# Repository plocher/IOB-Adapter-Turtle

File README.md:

# IOB-Adapter-Generic
## License: CERN Open Hardware Licence v1.2

IOB Personality: Turtle Tortoise adapter

A 5x2 plug-in with 3x inputs and one output (Motor control, feedback for N, R and Occupancy)

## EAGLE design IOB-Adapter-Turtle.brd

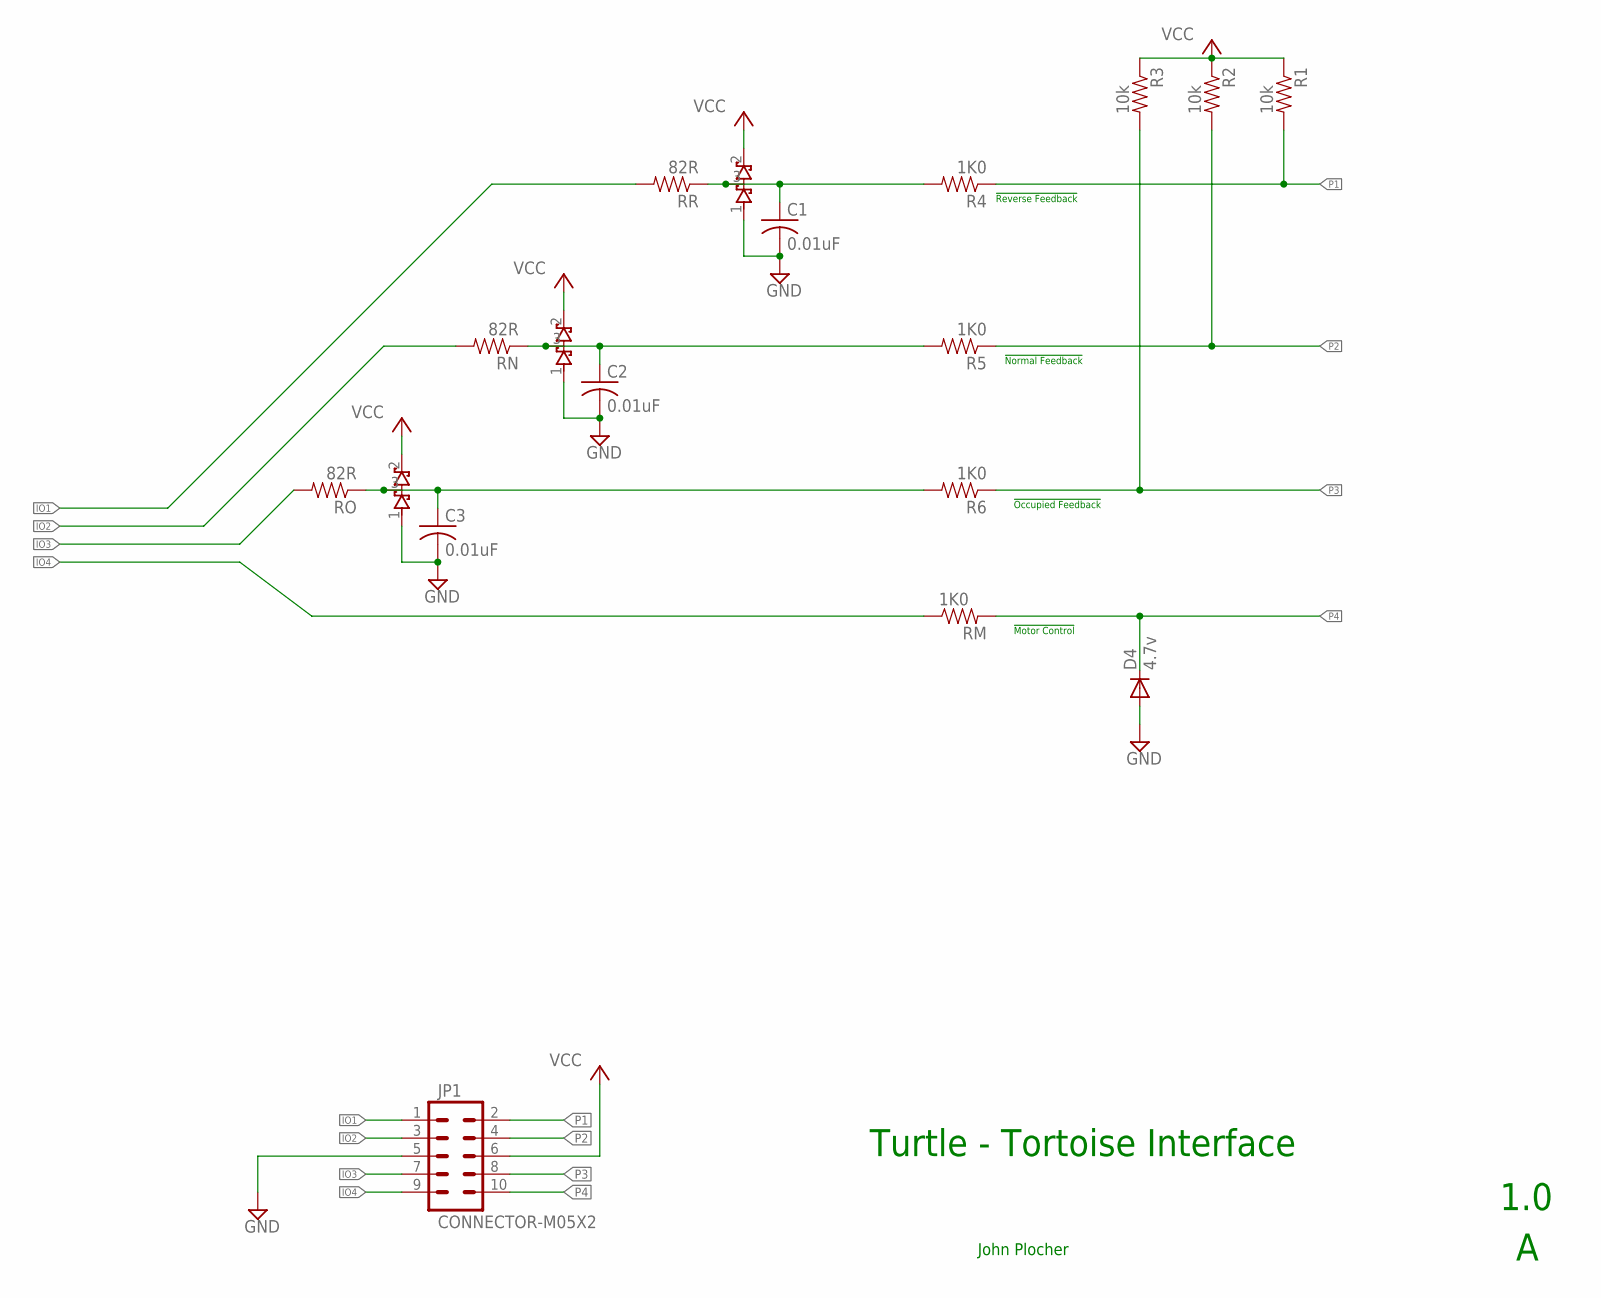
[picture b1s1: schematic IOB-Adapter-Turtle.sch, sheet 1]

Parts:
C1, C2, C3: 0.01uF; 0603-CAP
D1, D2, D3: BAT54S; SOT23
D4: 4.7v; SOT23
JP1: CONNECTOR-M05X2; IOB-V3-MODULE
R1, R2, R3: 10k; 0805-RES
R4, R5, R6: 1K0; 0603-RES
RM: 1K0; 0603-RES
RN: 82R; 0805-RES
RO: 82R; 0805-RES
RR: 82R; 0805-RES

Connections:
GND: C1.2, C2.2, C3.2, D1.1 (A1), D2.1 (A1), D3.1 (A1), D4.1 (A), JP1.5
IO1: JP1.1, RR.2
IO2: JP1.3, RN.2
IO3: JP1.7, RO.2
IO4: JP1.9, RM.1
unnamed: C2.1, D2.3 (COM), R5.2, RN.1
unnamed: C1.1, D1.3 (COM), R4.2, RR.1
unnamed: C3.1, D3.3 (COM), R6.2, RO.1
P1: JP1.2, R1.2, R4.1
P2: JP1.4, R2.2, R5.1
P3: JP1.8, R3.2, R6.1
P4: D4.3 (C), JP1.10, RM.2
VCC: D1.2 (C2), D2.2 (C2), D3.2 (C2), JP1.6, R1.1, R2.1, R3.1

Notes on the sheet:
Turtle - Tortoise Interface
1.0
John Plocher
!Normal Feedback
!Reverse Feedback
!Occupied Feedback
!Motor Control

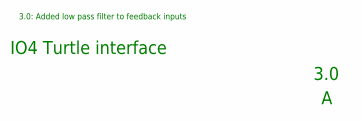
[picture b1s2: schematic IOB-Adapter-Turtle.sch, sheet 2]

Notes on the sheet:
IO4 Turtle interface
3.0
3.0: Added low pass filter to feedback inputs

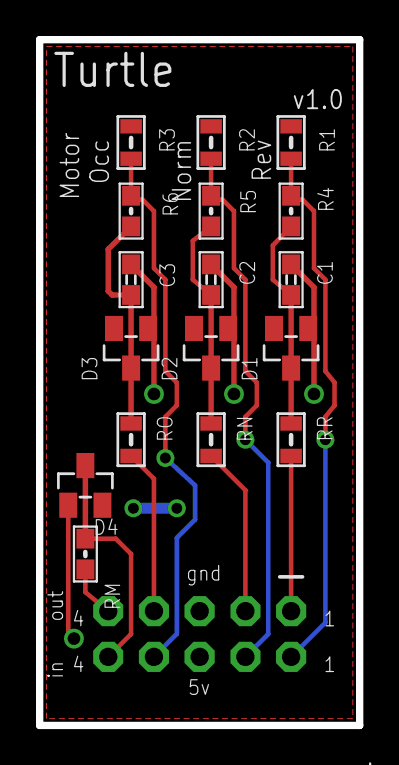
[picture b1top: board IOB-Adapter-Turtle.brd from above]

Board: 2 copper layers, 17.8 x 38.1 mm, 18 parts (1 on the bottom side), 13 nets.

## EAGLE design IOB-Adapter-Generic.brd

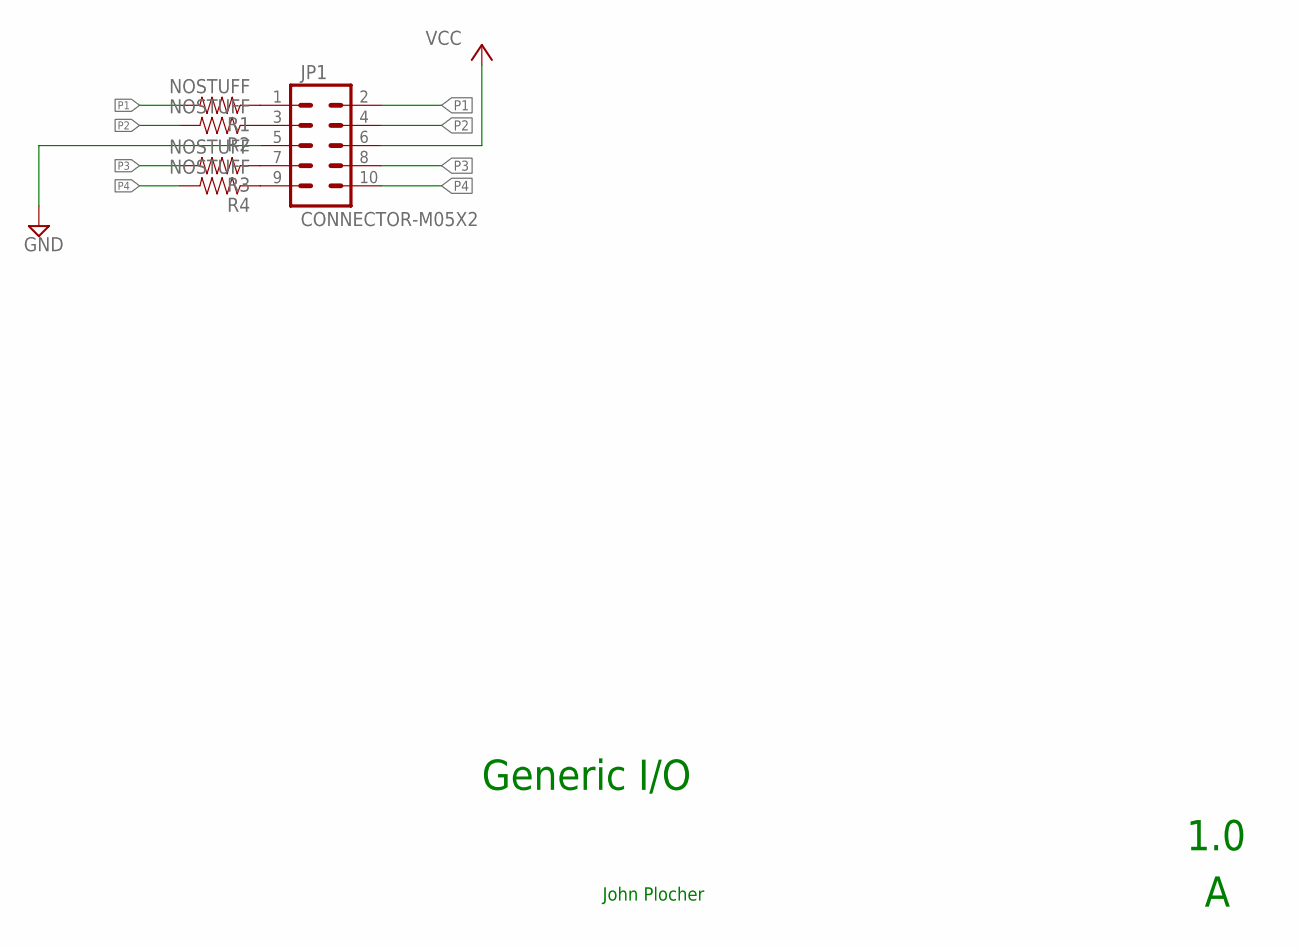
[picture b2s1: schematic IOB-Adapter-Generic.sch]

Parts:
JP1: CONNECTOR-M05X2; IOB-V3-MODULE
R1, R2, R3, R4: NOSTUFF; CUT-R

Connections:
GND: JP1.5
unnamed: JP1.1, R1.P2 (1)
unnamed: JP1.3, R2.P2 (1)
unnamed: JP1.7, R3.P2 (1)
unnamed: JP1.9, R4.P2 (1)
P1: JP1.2, R1.P1 (2)
P2: JP1.4, R2.P1 (2)
P3: JP1.8, R3.P1 (2)
P4: JP1.10, R4.P1 (2)
VCC: JP1.6

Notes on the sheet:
Generic I/O
1.0
John Plocher

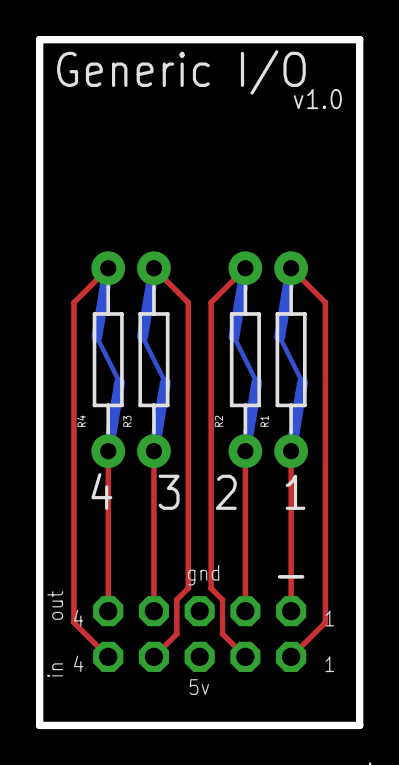
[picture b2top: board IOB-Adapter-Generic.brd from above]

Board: 2 copper layers, 17.8 x 38.1 mm, 5 parts (1 on the bottom side), 8 nets.

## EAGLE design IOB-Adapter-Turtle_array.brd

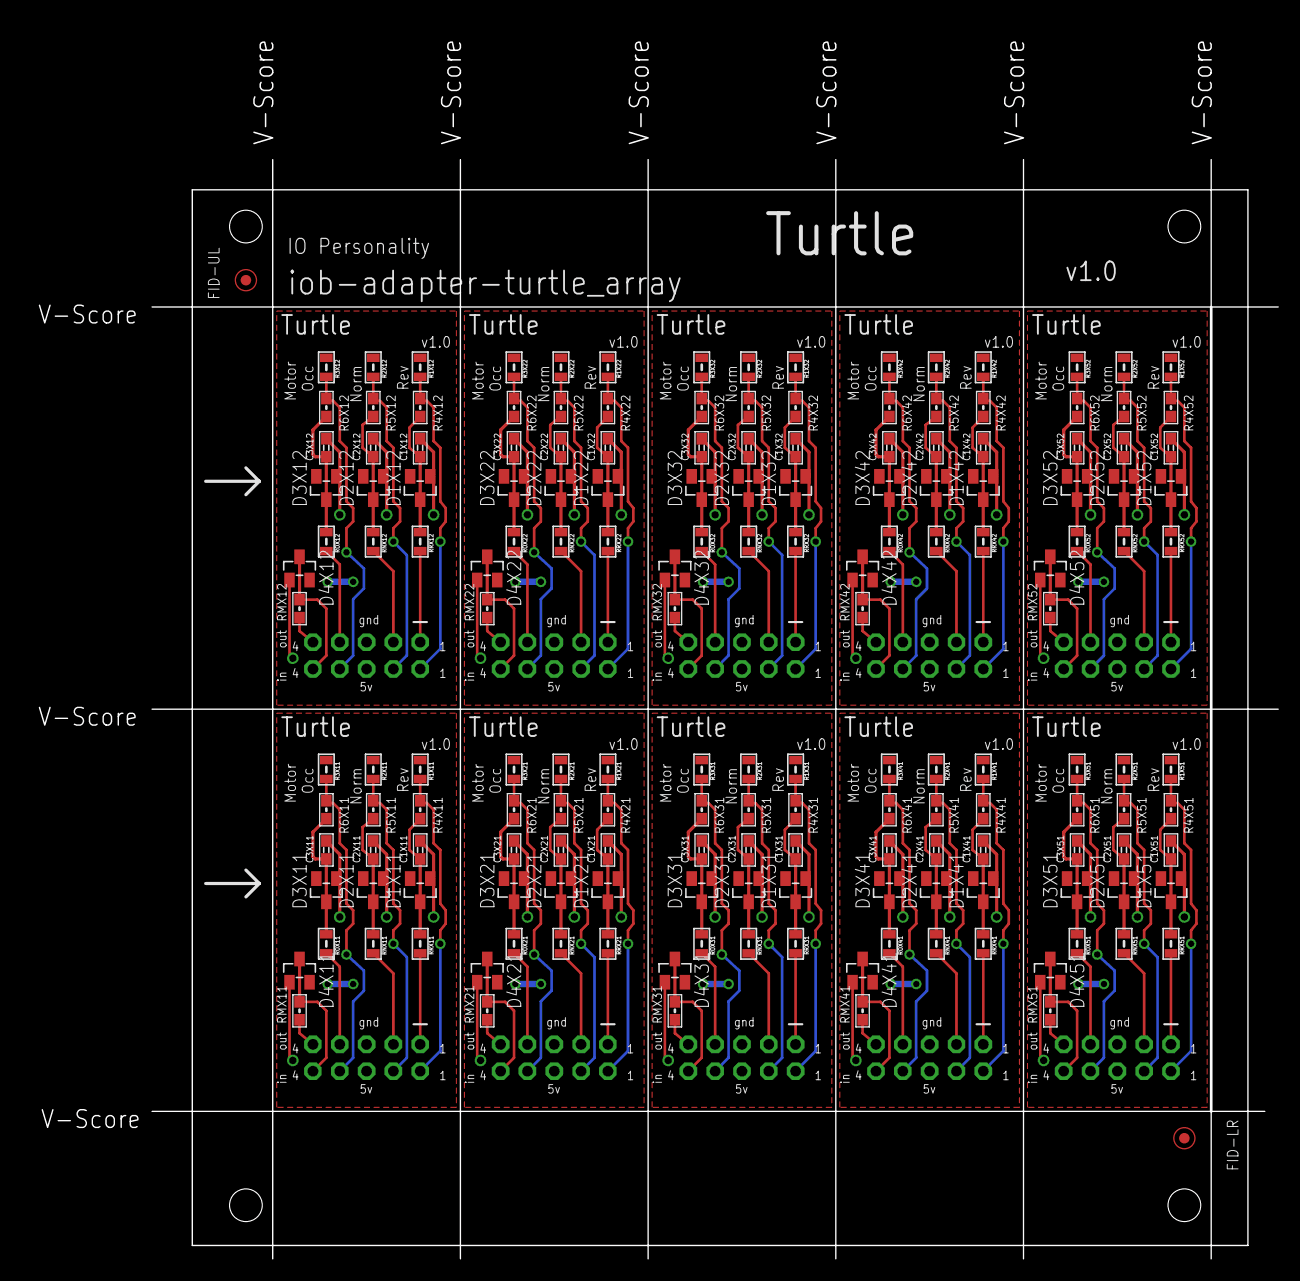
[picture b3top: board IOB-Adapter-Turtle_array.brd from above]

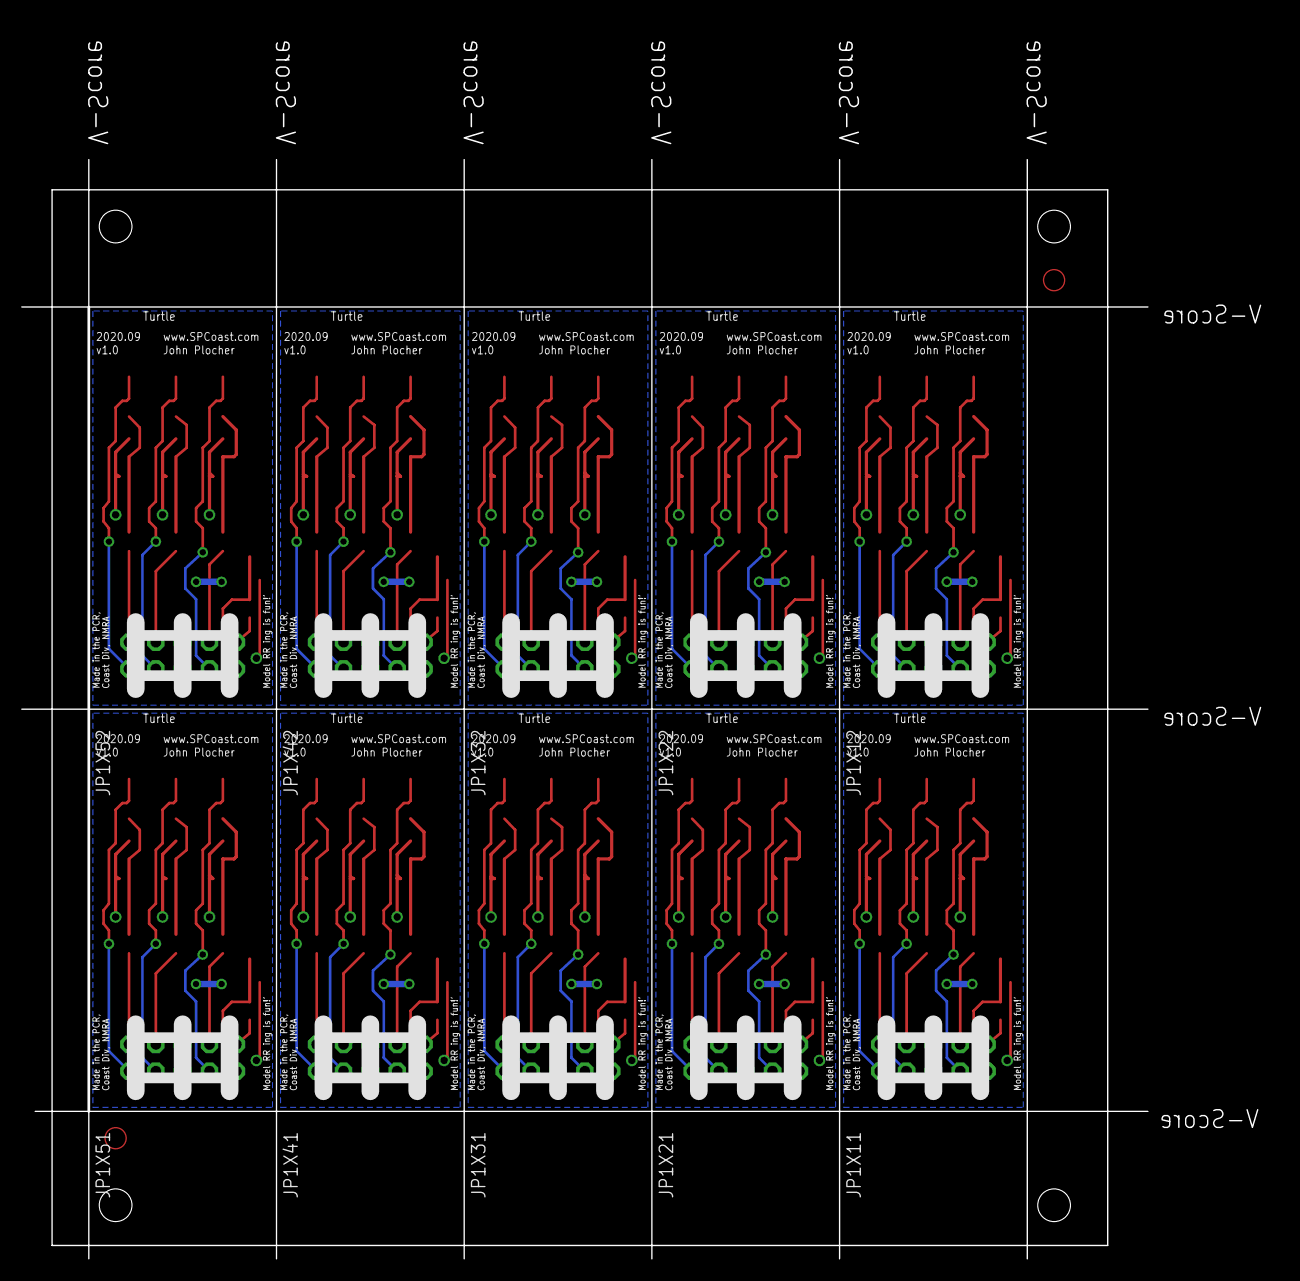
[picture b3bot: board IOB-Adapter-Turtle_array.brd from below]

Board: 2 copper layers, 118.9 x 117.1 mm, 183 parts (10 on the bottom side), 130 nets.

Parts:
C1X11, C1X12, C1X21, C1X22, C1X31, C1X32, C1X41, C1X42, C1X51, C1X52, C2X11, C2X12, C2X21, C2X22, C2X31, C2X32, C2X41, C2X42, C2X51, C2X52, C3X11, C3X12, C3X21, C3X22, C3X31, C3X32, C3X41, C3X42, C3X51, C3X52: 0.01uF; 0603-CAP
CARRIER: BOARD; BOARD-DINRAIL-3.17IN-5X2-IOP
D1X11, D1X12, D1X21, D1X22, D1X31, D1X32, D1X41, D1X42, D1X51, D1X52, D2X11, D2X12, D2X21, D2X22, D2X31, D2X32, D2X41, D2X42, D2X51, D2X52, D3X11, D3X12, D3X21, D3X22, D3X31, D3X32, D3X41, D3X42, D3X51, D3X52: BAT54S; SOT23
D4X11, D4X12, D4X21, D4X22, D4X31, D4X32, D4X41, D4X42, D4X51, D4X52: 4.7v; SOT23
FID-LR: FIDUCIAL; FIDUCIAL_1MM
FID-UL: FIDUCIAL; FIDUCIAL_1MM
JP1X11, JP1X12, JP1X21, JP1X22, JP1X31, JP1X32, JP1X41, JP1X42, JP1X51, JP1X52: CONNECTOR-M05X2; IOB-V3-MODULE
R1X11, R1X12, R1X21, R1X22, R1X31, R1X32, R1X41, R1X42, R1X51, R1X52, R2X11, R2X12, R2X21, R2X22, R2X31, R2X32, R2X41, R2X42, R2X51, R2X52, R3X11, R3X12, R3X21, R3X22, R3X31, R3X32, R3X41, R3X42, R3X51, R3X52: 10k; 0805-RES
R4X11, R4X12, R4X21, R4X22, R4X31, R4X32, R4X41, R4X42, R4X51, R4X52, R5X11, R5X12, R5X21, R5X22, R5X31, R5X32, R5X41, R5X42, R5X51, R5X52, R6X11, R6X12, R6X21, R6X22, R6X31, R6X32, R6X41, R6X42, R6X51, R6X52: 1K0; 0603-RES
RMX11, RMX12, RMX21, RMX22, RMX31, RMX32, RMX41, RMX42, RMX51, RMX52: 1K0; 0603-RES
RNX11, RNX12, RNX21, RNX22, RNX31, RNX32, RNX41, RNX42, RNX51, RNX52: 82R; 0805-RES
ROX11, ROX12, ROX21, ROX22, ROX31, ROX32, ROX41, ROX42, ROX51, ROX52: 82R; 0805-RES
RRX11, RRX12, RRX21, RRX22, RRX31, RRX32, RRX41, RRX42, RRX51, RRX52: 82R; 0805-RES

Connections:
GNDX11: C1X11.2, C2X11.2, C3X11.2, D1X11.1, D2X11.1, D3X11.1, D4X11.1, JP1X11.5
GNDX12: C1X12.2, C2X12.2, C3X12.2, D1X12.1, D2X12.1, D3X12.1, D4X12.1, JP1X12.5
GNDX21: C1X21.2, C2X21.2, C3X21.2, D1X21.1, D2X21.1, D3X21.1, D4X21.1, JP1X21.5
GNDX22: C1X22.2, C2X22.2, C3X22.2, D1X22.1, D2X22.1, D3X22.1, D4X22.1, JP1X22.5
GNDX31: C1X31.2, C2X31.2, C3X31.2, D1X31.1, D2X31.1, D3X31.1, D4X31.1, JP1X31.5
GNDX32: C1X32.2, C2X32.2, C3X32.2, D1X32.1, D2X32.1, D3X32.1, D4X32.1, JP1X32.5
GNDX41: C1X41.2, C2X41.2, C3X41.2, D1X41.1, D2X41.1, D3X41.1, D4X41.1, JP1X41.5
GNDX42: C1X42.2, C2X42.2, C3X42.2, D1X42.1, D2X42.1, D3X42.1, D4X42.1, JP1X42.5
GNDX51: C1X51.2, C2X51.2, C3X51.2, D1X51.1, D2X51.1, D3X51.1, D4X51.1, JP1X51.5
GNDX52: C1X52.2, C2X52.2, C3X52.2, D1X52.1, D2X52.1, D3X52.1, D4X52.1, JP1X52.5
IO1X11: JP1X11.1, RRX11.2
IO1X12: JP1X12.1, RRX12.2
IO1X21: JP1X21.1, RRX21.2
IO1X22: JP1X22.1, RRX22.2
IO1X31: JP1X31.1, RRX31.2
IO1X32: JP1X32.1, RRX32.2
IO1X41: JP1X41.1, RRX41.2
IO1X42: JP1X42.1, RRX42.2
IO1X51: JP1X51.1, RRX51.2
IO1X52: JP1X52.1, RRX52.2
IO2X11: JP1X11.3, RNX11.2
IO2X12: JP1X12.3, RNX12.2
IO2X21: JP1X21.3, RNX21.2
IO2X22: JP1X22.3, RNX22.2
IO2X31: JP1X31.3, RNX31.2
IO2X32: JP1X32.3, RNX32.2
IO2X41: JP1X41.3, RNX41.2
IO2X42: JP1X42.3, RNX42.2
IO2X51: JP1X51.3, RNX51.2
IO2X52: JP1X52.3, RNX52.2
IO3X11: JP1X11.7, ROX11.2
IO3X12: JP1X12.7, ROX12.2
IO3X21: JP1X21.7, ROX21.2
IO3X22: JP1X22.7, ROX22.2
IO3X31: JP1X31.7, ROX31.2
IO3X32: JP1X32.7, ROX32.2
IO3X41: JP1X41.7, ROX41.2
IO3X42: JP1X42.7, ROX42.2
IO3X51: JP1X51.7, ROX51.2
IO3X52: JP1X52.7, ROX52.2
IO4X11: JP1X11.9, RMX11.1
IO4X12: JP1X12.9, RMX12.1
IO4X21: JP1X21.9, RMX21.1
IO4X22: JP1X22.9, RMX22.1
IO4X31: JP1X31.9, RMX31.1
IO4X32: JP1X32.9, RMX32.1
IO4X41: JP1X41.9, RMX41.1
IO4X42: JP1X42.9, RMX42.1
IO4X51: JP1X51.9, RMX51.1
IO4X52: JP1X52.9, RMX52.1
unnamed: C2X11.1, D2X11.3, R5X11.2, RNX11.1
unnamed: C2X12.1, D2X12.3, R5X12.2, RNX12.1
unnamed: C2X21.1, D2X21.3, R5X21.2, RNX21.1
unnamed: C2X22.1, D2X22.3, R5X22.2, RNX22.1
unnamed: C2X31.1, D2X31.3, R5X31.2, RNX31.1
unnamed: C2X32.1, D2X32.3, R5X32.2, RNX32.1
unnamed: C2X41.1, D2X41.3, R5X41.2, RNX41.1
unnamed: C2X42.1, D2X42.3, R5X42.2, RNX42.1
unnamed: C2X51.1, D2X51.3, R5X51.2, RNX51.1
unnamed: C2X52.1, D2X52.3, R5X52.2, RNX52.1
unnamed: C1X11.1, D1X11.3, R4X11.2, RRX11.1
unnamed: C1X12.1, D1X12.3, R4X12.2, RRX12.1
unnamed: C1X21.1, D1X21.3, R4X21.2, RRX21.1
unnamed: C1X22.1, D1X22.3, R4X22.2, RRX22.1
unnamed: C1X31.1, D1X31.3, R4X31.2, RRX31.1
unnamed: C1X32.1, D1X32.3, R4X32.2, RRX32.1
unnamed: C1X41.1, D1X41.3, R4X41.2, RRX41.1
unnamed: C1X42.1, D1X42.3, R4X42.2, RRX42.1
unnamed: C1X51.1, D1X51.3, R4X51.2, RRX51.1
unnamed: C1X52.1, D1X52.3, R4X52.2, RRX52.1
unnamed: C3X11.1, D3X11.3, R6X11.2, ROX11.1
unnamed: C3X12.1, D3X12.3, R6X12.2, ROX12.1
unnamed: C3X21.1, D3X21.3, R6X21.2, ROX21.1
unnamed: C3X22.1, D3X22.3, R6X22.2, ROX22.1
unnamed: C3X31.1, D3X31.3, R6X31.2, ROX31.1
unnamed: C3X32.1, D3X32.3, R6X32.2, ROX32.1
unnamed: C3X41.1, D3X41.3, R6X41.2, ROX41.1
unnamed: C3X42.1, D3X42.3, R6X42.2, ROX42.1
unnamed: C3X51.1, D3X51.3, R6X51.2, ROX51.1
unnamed: C3X52.1, D3X52.3, R6X52.2, ROX52.1
P1X11: JP1X11.2, R1X11.2, R4X11.1
P1X12: JP1X12.2, R1X12.2, R4X12.1
P1X21: JP1X21.2, R1X21.2, R4X21.1
P1X22: JP1X22.2, R1X22.2, R4X22.1
P1X31: JP1X31.2, R1X31.2, R4X31.1
P1X32: JP1X32.2, R1X32.2, R4X32.1
P1X41: JP1X41.2, R1X41.2, R4X41.1
P1X42: JP1X42.2, R1X42.2, R4X42.1
P1X51: JP1X51.2, R1X51.2, R4X51.1
P1X52: JP1X52.2, R1X52.2, R4X52.1
P2X11: JP1X11.4, R2X11.2, R5X11.1
P2X12: JP1X12.4, R2X12.2, R5X12.1
P2X21: JP1X21.4, R2X21.2, R5X21.1
P2X22: JP1X22.4, R2X22.2, R5X22.1
P2X31: JP1X31.4, R2X31.2, R5X31.1
P2X32: JP1X32.4, R2X32.2, R5X32.1
P2X41: JP1X41.4, R2X41.2, R5X41.1
P2X42: JP1X42.4, R2X42.2, R5X42.1
P2X51: JP1X51.4, R2X51.2, R5X51.1
P2X52: JP1X52.4, R2X52.2, R5X52.1
P3X11: JP1X11.8, R3X11.2, R6X11.1
P3X12: JP1X12.8, R3X12.2, R6X12.1
P3X21: JP1X21.8, R3X21.2, R6X21.1
P3X22: JP1X22.8, R3X22.2, R6X22.1
P3X31: JP1X31.8, R3X31.2, R6X31.1
P3X32: JP1X32.8, R3X32.2, R6X32.1
P3X41: JP1X41.8, R3X41.2, R6X41.1
P3X42: JP1X42.8, R3X42.2, R6X42.1
P3X51: JP1X51.8, R3X51.2, R6X51.1
P3X52: JP1X52.8, R3X52.2, R6X52.1
P4X11: D4X11.3, JP1X11.10, RMX11.2
P4X12: D4X12.3, JP1X12.10, RMX12.2
P4X21: D4X21.3, JP1X21.10, RMX21.2
P4X22: D4X22.3, JP1X22.10, RMX22.2
P4X31: D4X31.3, JP1X31.10, RMX31.2
P4X32: D4X32.3, JP1X32.10, RMX32.2
P4X41: D4X41.3, JP1X41.10, RMX41.2
P4X42: D4X42.3, JP1X42.10, RMX42.2
P4X51: D4X51.3, JP1X51.10, RMX51.2
P4X52: D4X52.3, JP1X52.10, RMX52.2
VCCX11: D1X11.2, D2X11.2, D3X11.2, JP1X11.6, R1X11.1, R2X11.1, R3X11.1
VCCX12: D1X12.2, D2X12.2, D3X12.2, JP1X12.6, R1X12.1, R2X12.1, R3X12.1
VCCX21: D1X21.2, D2X21.2, D3X21.2, JP1X21.6, R1X21.1, R2X21.1, R3X21.1
VCCX22: D1X22.2, D2X22.2, D3X22.2, JP1X22.6, R1X22.1, R2X22.1, R3X22.1
VCCX31: D1X31.2, D2X31.2, D3X31.2, JP1X31.6, R1X31.1, R2X31.1, R3X31.1
VCCX32: D1X32.2, D2X32.2, D3X32.2, JP1X32.6, R1X32.1, R2X32.1, R3X32.1
VCCX41: D1X41.2, D2X41.2, D3X41.2, JP1X41.6, R1X41.1, R2X41.1, R3X41.1
VCCX42: D1X42.2, D2X42.2, D3X42.2, JP1X42.6, R1X42.1, R2X42.1, R3X42.1
VCCX51: D1X51.2, D2X51.2, D3X51.2, JP1X51.6, R1X51.1, R2X51.1, R3X51.1
VCCX52: D1X52.2, D2X52.2, D3X52.2, JP1X52.6, R1X52.1, R2X52.1, R3X52.1

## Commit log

2020-09-17 Initial version
2020-09-18 Turtle layout, not generic...
2020-09-18 silkscreen tweeks
2020-10-05 added values for connectors
2020-10-06 normalized values
